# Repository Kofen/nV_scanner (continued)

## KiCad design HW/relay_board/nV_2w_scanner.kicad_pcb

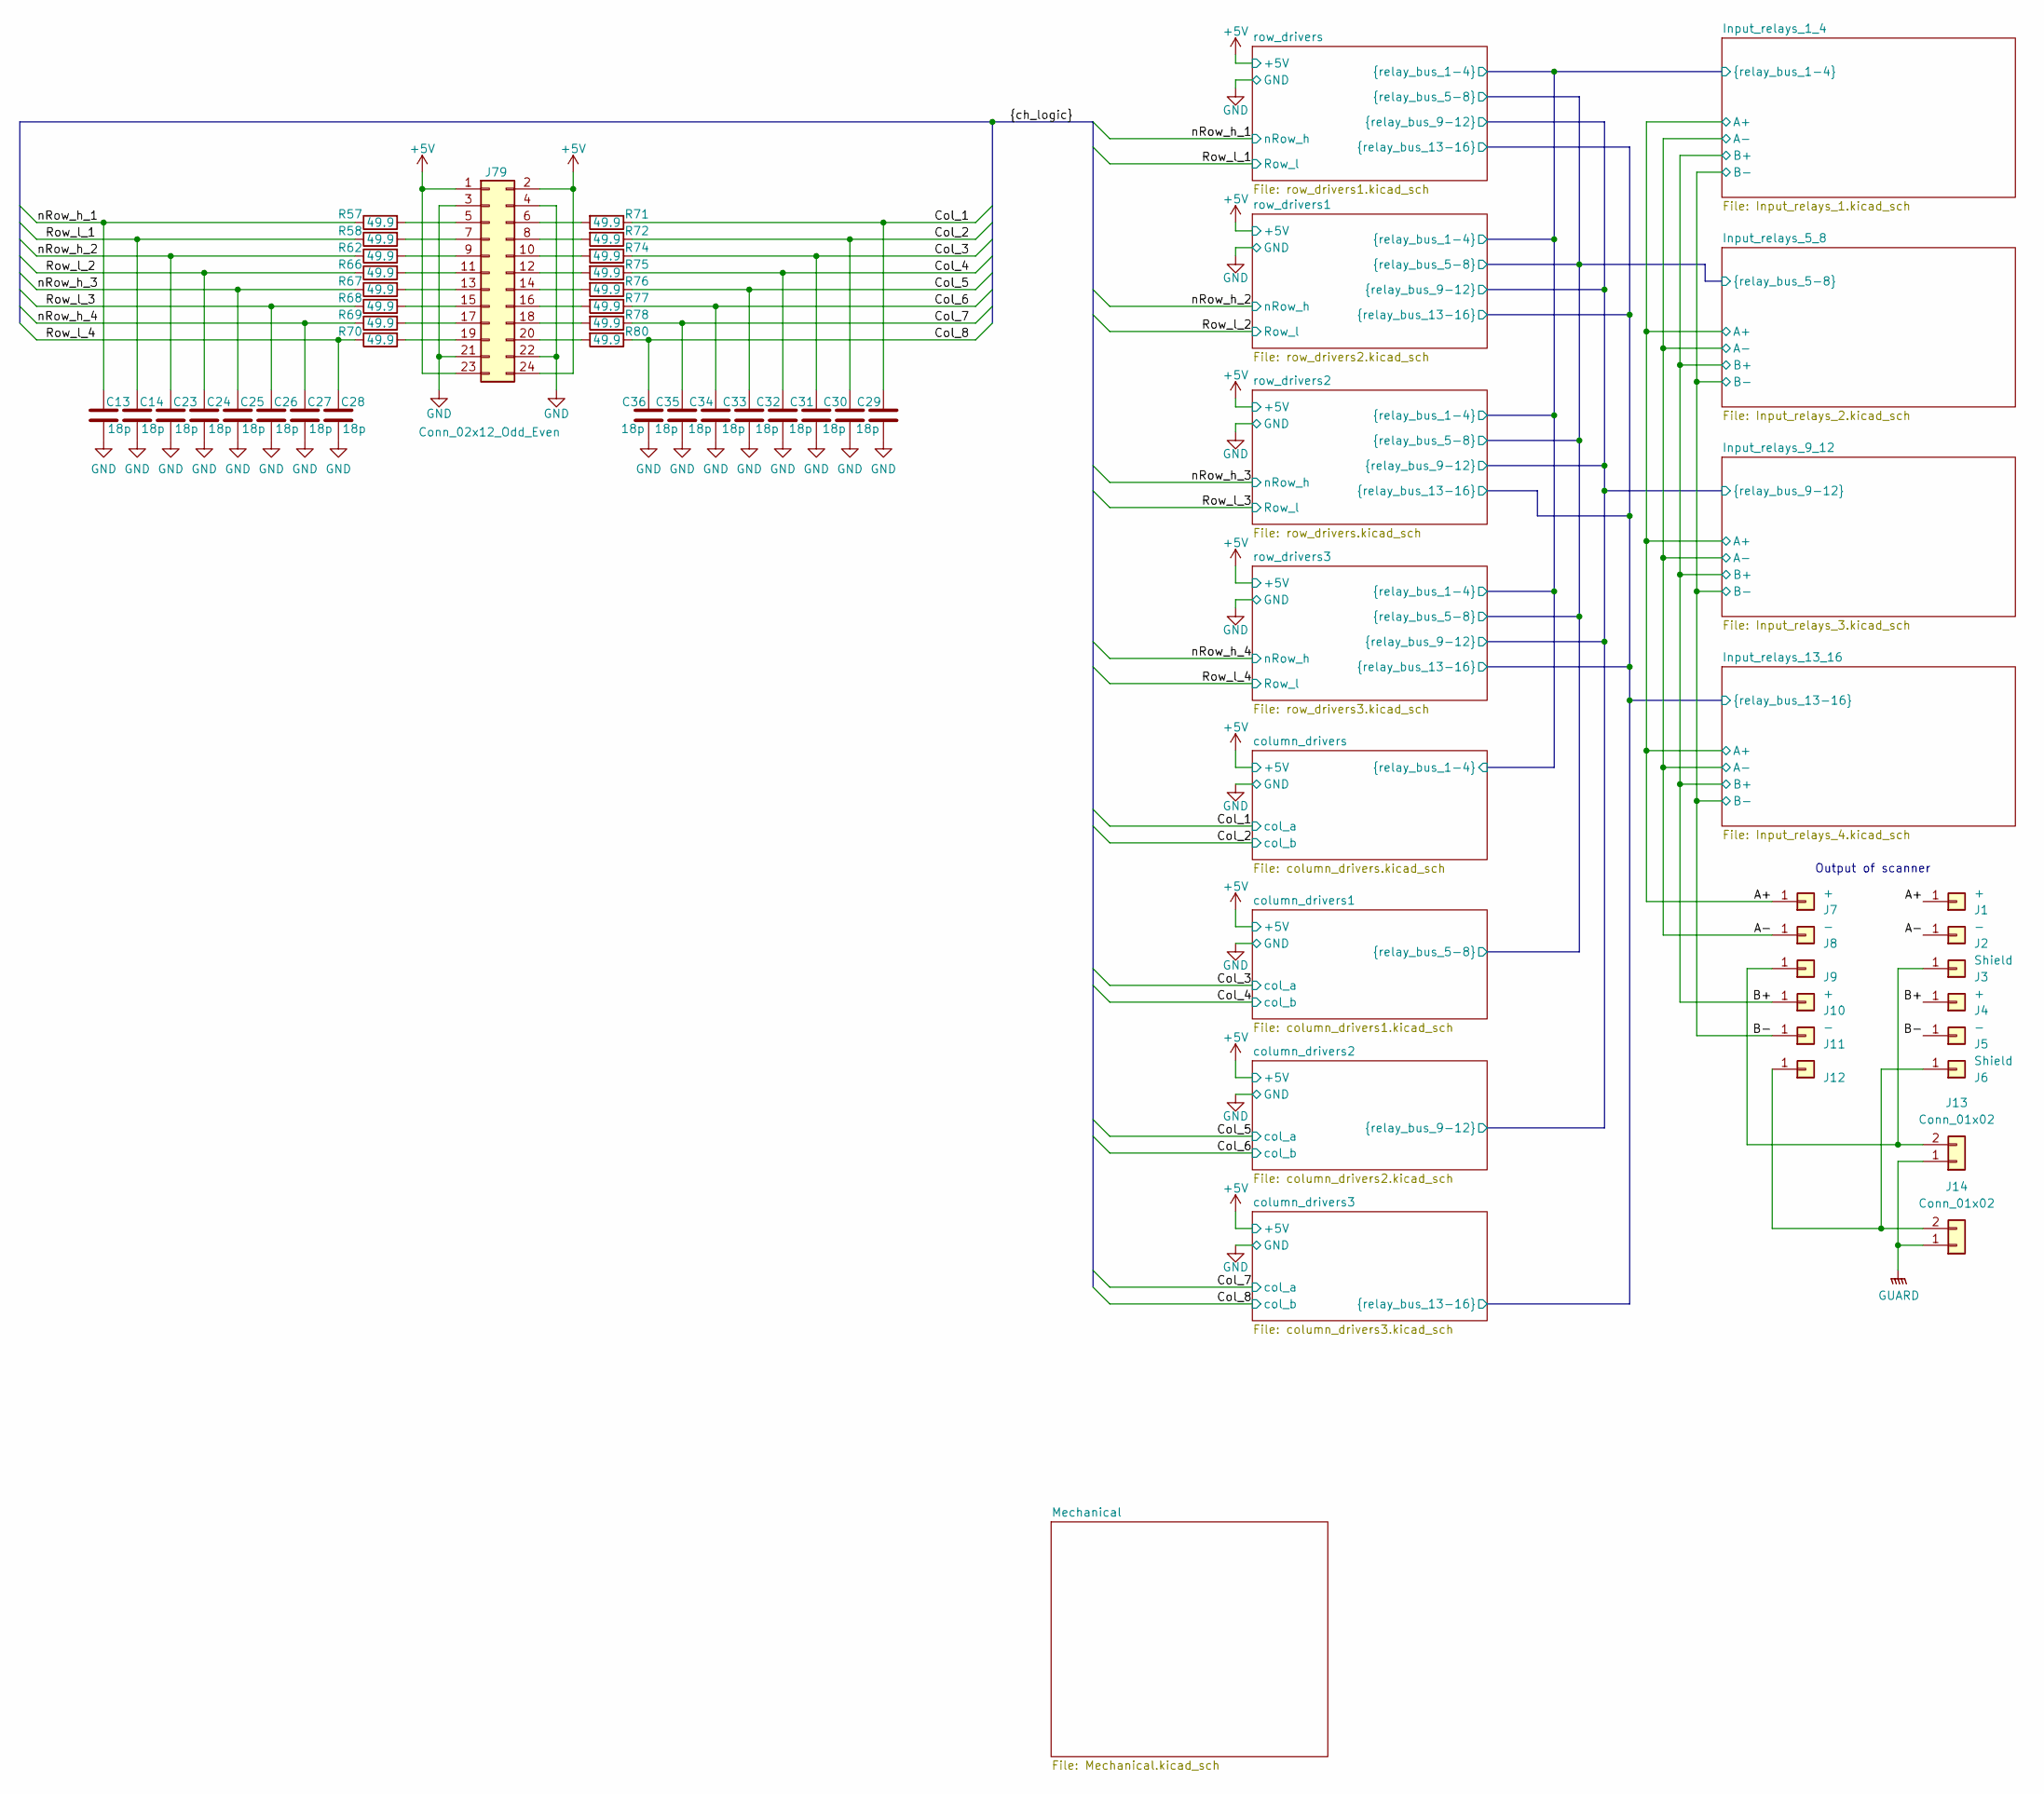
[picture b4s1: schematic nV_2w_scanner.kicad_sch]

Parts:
C13, C14, C23, C24, C25, C26, C27, C28, C29, C30, C31, C32, C33, C34, C35, C36: 18p; C_0402_1005Metric; JLCPCB C1549
J1, J4, J7, J10: +; SolderWirePad_1x01_SMD_3x5mm
J2, J5, J8, J11: -; SolderWirePad_1x01_SMD_3x5mm
J3, J6, J9, J12: Shield; SolderWirePad_1x01_SMD_3x5mm
J13, J14: Conn_01x02; PinHeader_1x02_P2.54mm_Vertical
J79: Conn_02x12_Odd_Even; PinHeader_2x12_P2.54mm_Vertical
R57, R58, R62, R66, R67, R68, R69, R70, R71, R72, R74, R75, R76, R77, R78, R80: 49.9; R_0402_1005Metric

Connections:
+5V: J79.1, J79.2, J79.23, J79.24; also elsewhere on the board
/A+: J1.1, J7.1; also elsewhere on the board
/A-: J2.1, J8.1; also elsewhere on the board
/B+: J4.1, J10.1; also elsewhere on the board
/B-: J5.1, J11.1; also elsewhere on the board
/Col_1: C29.1, R71.1; also elsewhere on the board
/Col_2: C30.1, R72.1; also elsewhere on the board
/Col_3: C31.1, R74.1; also elsewhere on the board
/Col_4: C32.1, R75.1; also elsewhere on the board
/Col_5: C33.1, R76.1; also elsewhere on the board
/Col_6: C34.1, R77.1; also elsewhere on the board
/Col_7: C35.1, R78.1; also elsewhere on the board
/Col_8: C36.1, R80.1; also elsewhere on the board
/Row_l_1: C14.1, R58.1; also elsewhere on the board
/Row_l_2: C24.1, R66.1; also elsewhere on the board
/Row_l_3: C26.1, R68.1; also elsewhere on the board
/Row_l_4: C28.1, R70.1; also elsewhere on the board
/nRow_h_1: C13.1, R57.1; also elsewhere on the board
/nRow_h_2: C23.1, R62.1; also elsewhere on the board
/nRow_h_3: C25.1, R67.1; also elsewhere on the board
/nRow_h_4: C27.1, R69.1; also elsewhere on the board
GND: C13.2, C14.2, C23.2, C24.2, C25.2, C26.2, C27.2, C28.2, C29.2, C30.2, C31.2, C32.2, C33.2, C34.2, C35.2, C36.2, J79.3, J79.4, J79.21, J79.22; also elsewhere on the board
GUARD: J13.1, J14.1; also elsewhere on the board
unnamed: J6.1, J12.1, J14.2
unnamed: J3.1, J9.1, J13.2
unnamed: J79.5, R57.2
unnamed: J79.6, R71.2
unnamed: J79.7, R58.2
unnamed: J79.8, R72.2
unnamed: J79.9, R62.2
unnamed: J79.10, R74.2
unnamed: J79.11, R66.2
unnamed: J79.12, R75.2
unnamed: J79.13, R67.2
unnamed: J79.14, R76.2
unnamed: J79.15, R68.2
unnamed: J79.16, R77.2
unnamed: J79.17, R69.2
unnamed: J79.18, R78.2
unnamed: J79.19, R70.2
unnamed: J79.20, R80.2

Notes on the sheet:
Output of scanner

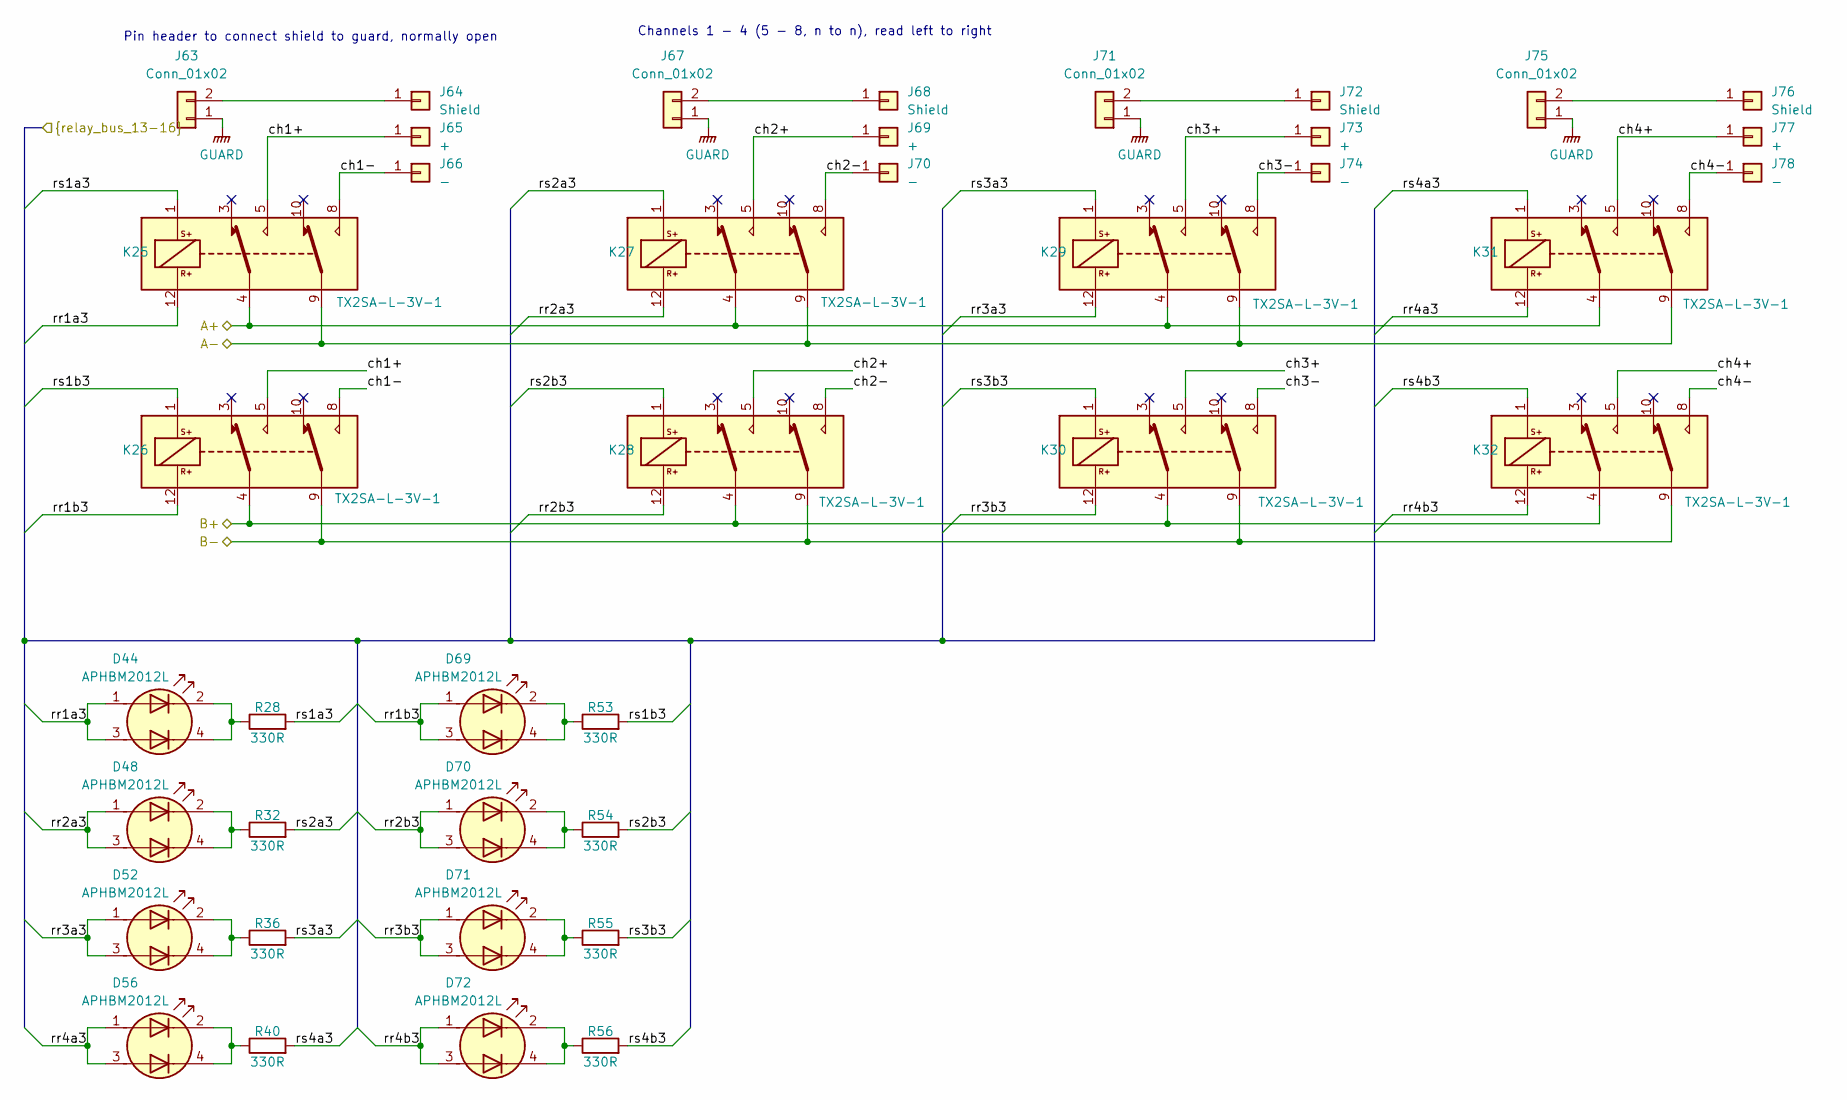
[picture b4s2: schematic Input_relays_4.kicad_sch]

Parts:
D44, D48, D52, D56, D69, D70, D71, D72: APHBM2012L; LED_Kingbright_APHBM2012_2x1.25mm
J63, J67, J71, J75: Conn_01x02; PinHeader_1x02_P2.54mm_Vertical
J64, J68, J72, J76: Shield; SolderWirePad_1x01_SMD_3x5mm
J65, J69, J73, J77: +; SolderWirePad_1x01_SMD_3x5mm
J66, J70, J74, J78: -; SolderWirePad_1x01_SMD_3x5mm
K25, K26, K27, K28, K29, K30, K31, K32: TX2SA-L-3V-1; Relay_DPDT_Omron_G6S-2F
R28, R32, R36, R40, R53, R54, R55, R56: 330R; R_0603_1608Metric

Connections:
/A+: K25.4, K27.4, K29.4, K31.4; also elsewhere on the board
/A-: K25.9, K27.9, K29.9, K31.9; also elsewhere on the board
/B+: K26.4, K28.4, K30.4, K32.4; also elsewhere on the board
/B-: K26.9, K28.9, K30.9, K32.9; also elsewhere on the board
/Input_relays_13_16/ch1+: J65.1, K25.5, K26.5
/Input_relays_13_16/ch1-: J66.1, K25.8, K26.8
/Input_relays_13_16/ch2+: J69.1, K27.5, K28.5
/Input_relays_13_16/ch2-: J70.1, K27.8, K28.8
/Input_relays_13_16/ch3+: J73.1, K29.5, K30.5
/Input_relays_13_16/ch3-: J74.1, K29.8, K30.8
/Input_relays_13_16/ch4+: J77.1, K31.5, K32.5
/Input_relays_13_16/ch4-: J78.1, K31.8, K32.8
/Input_relays_13_16/rr1a3: D44.1 (A1), D44.3 (A2), K25.12; also elsewhere on the board
/Input_relays_13_16/rr1b3: D69.1 (A1), D69.3 (A2), K26.12; also elsewhere on the board
/Input_relays_13_16/rr2a3: D48.1 (A1), D48.3 (A2), K27.12; also elsewhere on the board
/Input_relays_13_16/rr2b3: D70.1 (A1), D70.3 (A2), K28.12; also elsewhere on the board
/Input_relays_13_16/rr3a3: D52.1 (A1), D52.3 (A2), K29.12; also elsewhere on the board
/Input_relays_13_16/rr3b3: D71.1 (A1), D71.3 (A2), K30.12; also elsewhere on the board
/Input_relays_13_16/rr4a3: D56.1 (A1), D56.3 (A2), K31.12; also elsewhere on the board
/Input_relays_13_16/rr4b3: D72.1 (A1), D72.3 (A2), K32.12; also elsewhere on the board
/Input_relays_13_16/rs4a3: K25.1, K27.1, K29.1, K31.1, R28.2, R32.2, R36.2, R40.2; also elsewhere on the board
/Input_relays_13_16/rs4b3: K26.1, K28.1, K30.1, K32.1, R53.2, R54.2, R55.2, R56.2; also elsewhere on the board
GUARD: J63.1, J67.1, J71.1, J75.1; also elsewhere on the board
unnamed: D44.2 (K1), D44.4 (K2), R28.1
unnamed: D48.2 (K1), D48.4 (K2), R32.1
unnamed: D52.2 (K1), D52.4 (K2), R36.1
unnamed: D56.2 (K1), D56.4 (K2), R40.1
unnamed: D69.2 (K1), D69.4 (K2), R53.1
unnamed: D70.2 (K1), D70.4 (K2), R54.1
unnamed: D71.2 (K1), D71.4 (K2), R55.1
unnamed: D72.2 (K1), D72.4 (K2), R56.1
unnamed: J63.2, J64.1
unnamed: J67.2, J68.1
unnamed: J71.2, J72.1
unnamed: J75.2, J76.1

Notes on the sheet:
Pin header to connect shield to guard, normally open
Channels 1 - 4 (5 - 8, n to n), read left to right

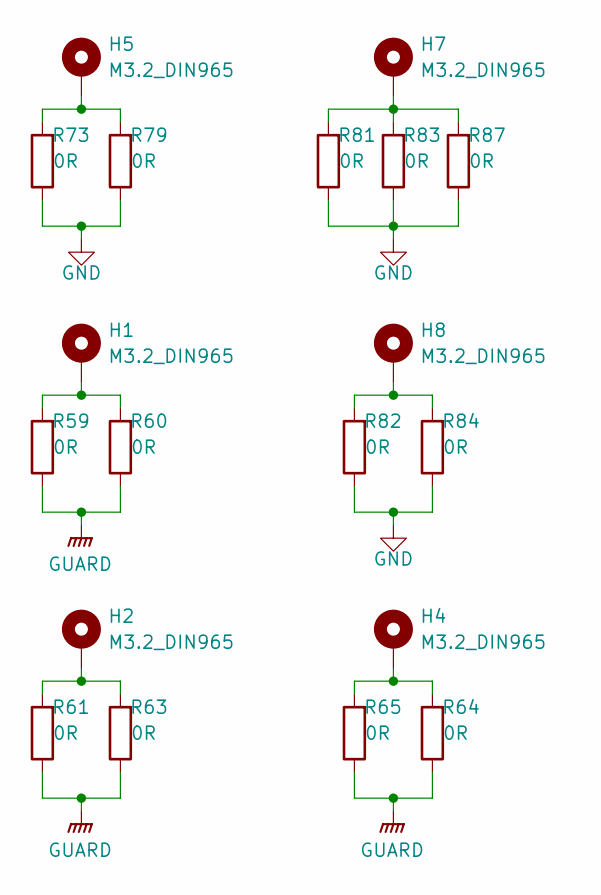
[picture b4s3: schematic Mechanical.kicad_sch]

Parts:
H1, H2, H4, H5, H7, H8: M3.2_DIN965; MountingHole_3.2mm_M3_DIN965_Pad
R59, R60, R61, R63, R64, R65, R73, R79, R81, R82, R83, R84, R87: 0R; R_0805_2012Metric

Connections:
GND: R73.1, R79.1, R81.1, R82.1, R83.1, R84.1, R87.1; also elsewhere on the board
GUARD: R59.1, R60.1, R61.1, R63.1, R64.1, R65.1; also elsewhere on the board
unnamed: H1.1, R59.2, R60.2
unnamed: H2.1, R61.2, R63.2
unnamed: H4.1, R64.2, R65.2
unnamed: H5.1, R73.2, R79.2
unnamed: H7.1, R81.2, R83.2, R87.2
unnamed: H8.1, R82.2, R84.2

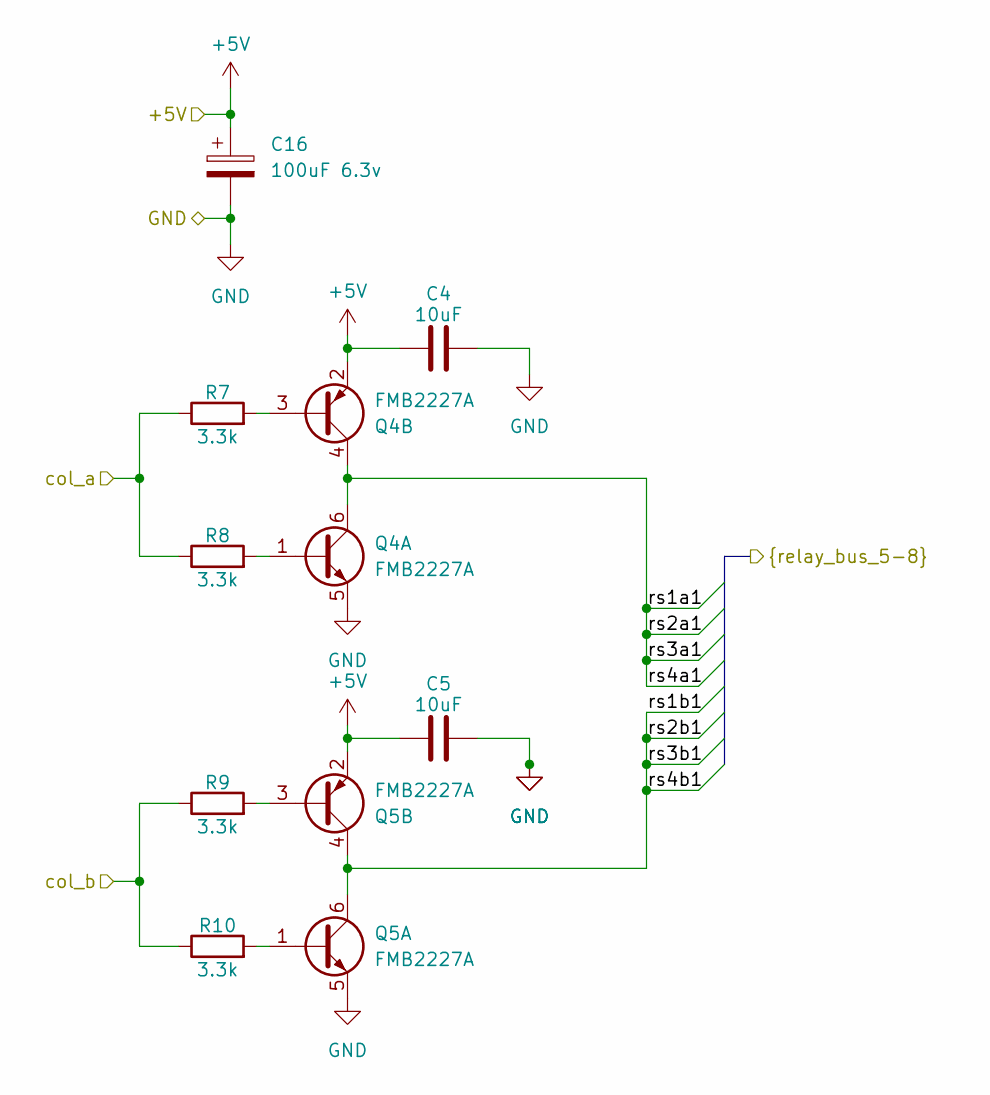
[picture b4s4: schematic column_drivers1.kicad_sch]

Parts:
C4, C5: 10uF; C_0603_1608Metric
C16: 100uF 6.3v; CP_EIA-7343-31_Kemet-D
Q4, Q5: FMB2227A; SuperSOT-6
R7, R8, R9, R10: 3.3k; R_0603_1608Metric

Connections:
+5V: C4.1, C5.1, C16.1, Q4.2 (E2), Q5.2 (E2); also elsewhere on the board
/Col_3: R7.1, R8.1; also elsewhere on the board
/Col_4: R9.1, R10.1; also elsewhere on the board
/Input_relays_5_8/rs2b1: Q5.4 (C2), Q5.6 (C1); also elsewhere on the board
/Input_relays_5_8/rs3a1: Q4.4 (C2), Q4.6 (C1); also elsewhere on the board
GND: C4.2, C5.2, C16.2, Q4.5 (E1), Q5.5 (E1); also elsewhere on the board
unnamed: Q4.1 (B1), R8.2
unnamed: Q4.3 (B2), R7.2
unnamed: Q5.1 (B1), R10.2
unnamed: Q5.3 (B2), R9.2

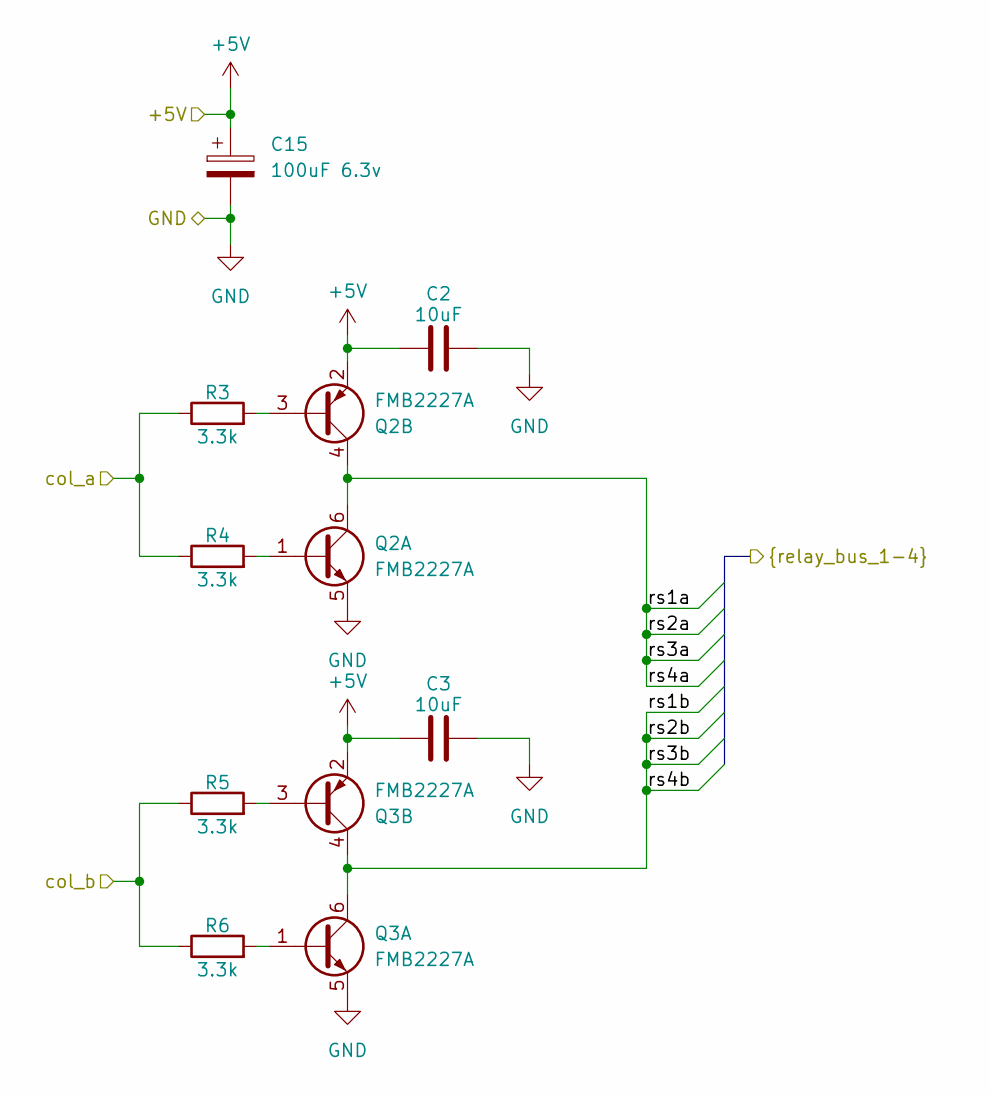
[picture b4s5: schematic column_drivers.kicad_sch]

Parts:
C2, C3: 10uF; C_0603_1608Metric
C15: 100uF 6.3v; CP_EIA-7343-31_Kemet-D
Q2, Q3: FMB2227A; SuperSOT-6
R3, R4, R5, R6: 3.3k; R_0603_1608Metric

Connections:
+5V: C2.1, C3.1, C15.1, Q2.2 (E2), Q3.2 (E2); also elsewhere on the board
/Col_1: R3.1, R4.1; also elsewhere on the board
/Col_2: R5.1, R6.1; also elsewhere on the board
/Input_relays_1_4/rs1a: Q2.4 (C2), Q2.6 (C1); also elsewhere on the board
/Input_relays_1_4/rs3b: Q3.4 (C2), Q3.6 (C1); also elsewhere on the board
GND: C2.2, C3.2, C15.2, Q2.5 (E1), Q3.5 (E1); also elsewhere on the board
unnamed: Q2.1 (B1), R4.2
unnamed: Q2.3 (B2), R3.2
unnamed: Q3.1 (B1), R6.2
unnamed: Q3.3 (B2), R5.2

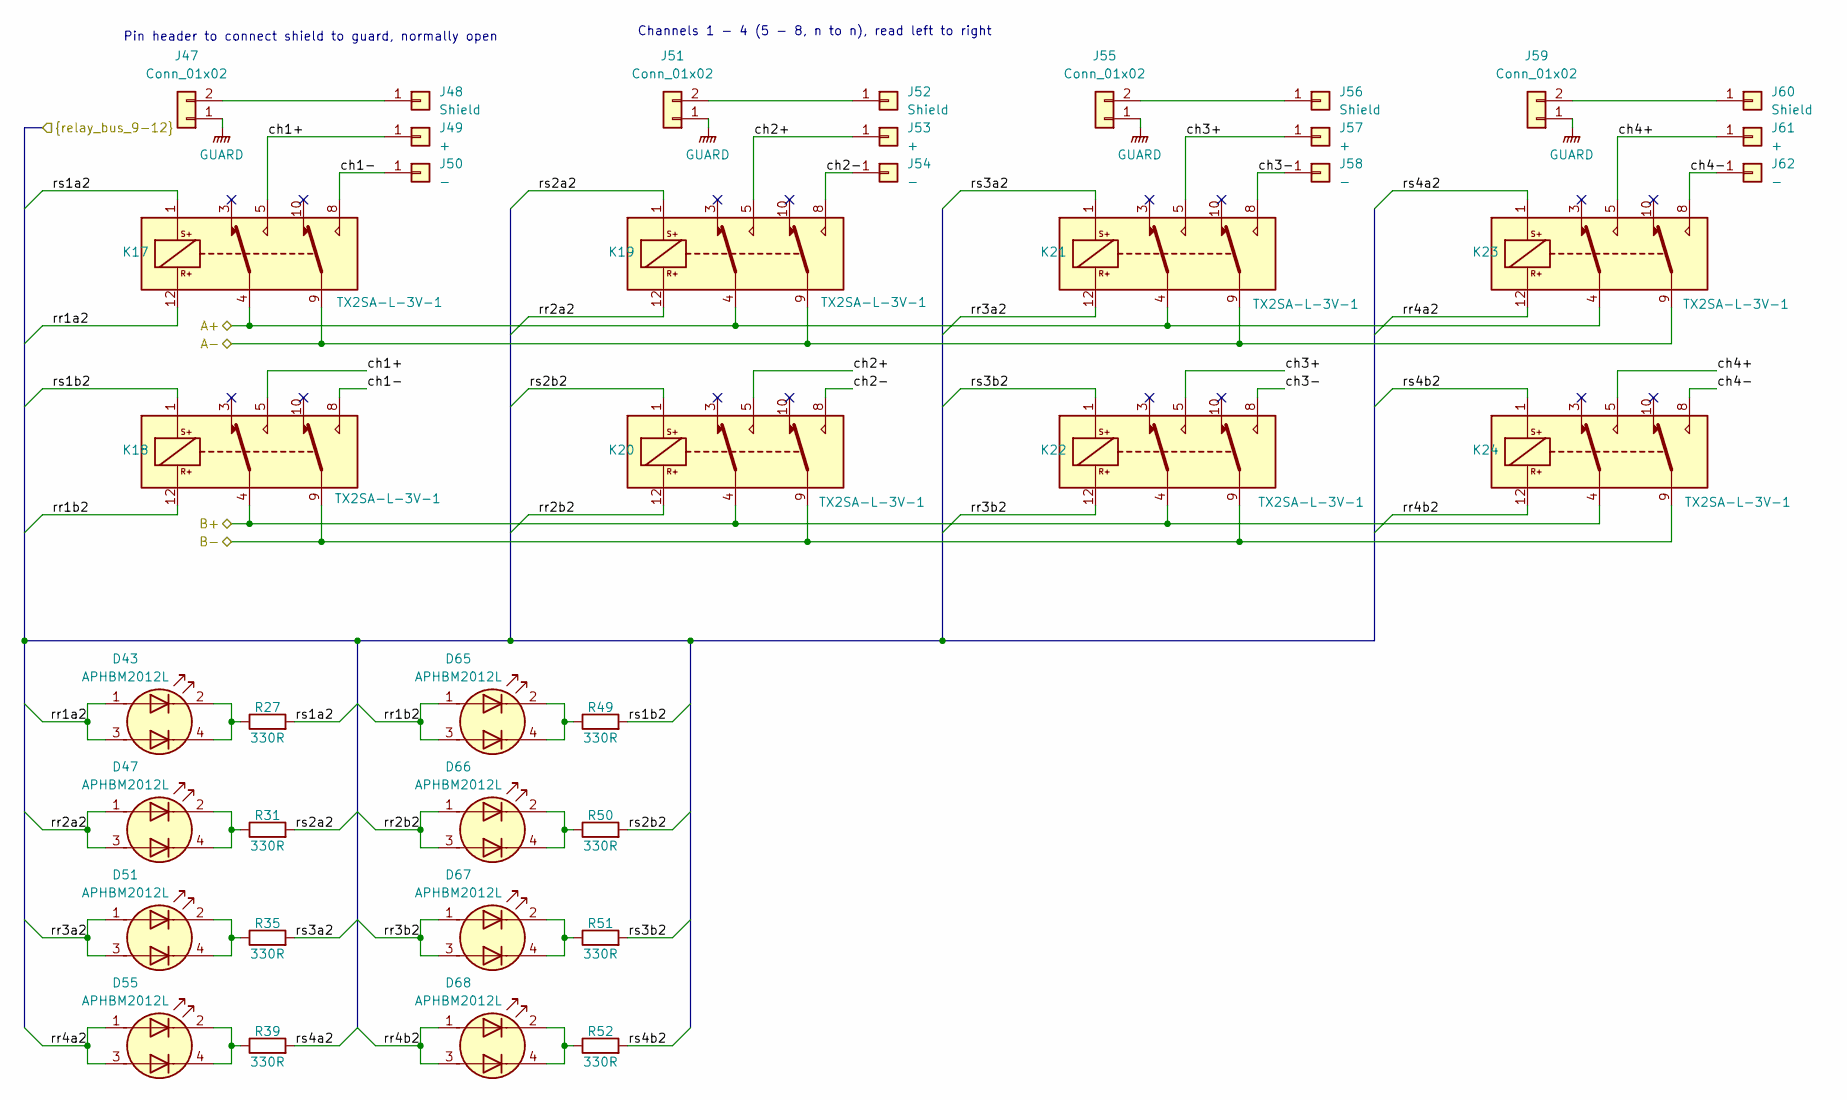
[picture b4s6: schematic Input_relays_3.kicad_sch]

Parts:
D43, D47, D51, D55, D65, D66, D67, D68: APHBM2012L; LED_Kingbright_APHBM2012_2x1.25mm
J47, J51, J55, J59: Conn_01x02; PinHeader_1x02_P2.54mm_Vertical
J48, J52, J56, J60: Shield; SolderWirePad_1x01_SMD_3x5mm
J49, J53, J57, J61: +; SolderWirePad_1x01_SMD_3x5mm
J50, J54, J58, J62: -; SolderWirePad_1x01_SMD_3x5mm
K17, K18, K19, K20, K21, K22, K23, K24: TX2SA-L-3V-1; Relay_DPDT_Omron_G6S-2F
R27, R31, R35, R39, R49, R50, R51, R52: 330R; R_0603_1608Metric

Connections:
/A+: K17.4, K19.4, K21.4, K23.4; also elsewhere on the board
/A-: K17.9, K19.9, K21.9, K23.9; also elsewhere on the board
/B+: K18.4, K20.4, K22.4, K24.4; also elsewhere on the board
/B-: K18.9, K20.9, K22.9, K24.9; also elsewhere on the board
/Input_relays_9_12/ch1+: J49.1, K17.5, K18.5
/Input_relays_9_12/ch1-: J50.1, K17.8, K18.8
/Input_relays_9_12/ch2+: J53.1, K19.5, K20.5
/Input_relays_9_12/ch2-: J54.1, K19.8, K20.8
/Input_relays_9_12/ch3+: J57.1, K21.5, K22.5
/Input_relays_9_12/ch3-: J58.1, K21.8, K22.8
/Input_relays_9_12/ch4+: J61.1, K23.5, K24.5
/Input_relays_9_12/ch4-: J62.1, K23.8, K24.8
/Input_relays_9_12/rr1a2: D43.1 (A1), D43.3 (A2), K17.12; also elsewhere on the board
/Input_relays_9_12/rr1b2: D65.1 (A1), D65.3 (A2), K18.12; also elsewhere on the board
/Input_relays_9_12/rr2a2: D47.1 (A1), D47.3 (A2), K19.12; also elsewhere on the board
/Input_relays_9_12/rr2b2: D66.1 (A1), D66.3 (A2), K20.12; also elsewhere on the board
/Input_relays_9_12/rr3a2: D51.1 (A1), D51.3 (A2), K21.12; also elsewhere on the board
/Input_relays_9_12/rr3b2: D67.1 (A1), D67.3 (A2), K22.12; also elsewhere on the board
/Input_relays_9_12/rr4a2: D55.1 (A1), D55.3 (A2), K23.12; also elsewhere on the board
/Input_relays_9_12/rr4b2: D68.1 (A1), D68.3 (A2), K24.12; also elsewhere on the board
/Input_relays_9_12/rs3a2: K17.1, K19.1, K21.1, K23.1, R27.2, R31.2, R35.2, R39.2; also elsewhere on the board
/Input_relays_9_12/rs3b2: K18.1, K20.1, K22.1, K24.1, R49.2, R50.2, R51.2, R52.2; also elsewhere on the board
GUARD: J47.1, J51.1, J55.1, J59.1; also elsewhere on the board
unnamed: D43.2 (K1), D43.4 (K2), R27.1
unnamed: D47.2 (K1), D47.4 (K2), R31.1
unnamed: D51.2 (K1), D51.4 (K2), R35.1
unnamed: D55.2 (K1), D55.4 (K2), R39.1
unnamed: D65.2 (K1), D65.4 (K2), R49.1
unnamed: D66.2 (K1), D66.4 (K2), R50.1
unnamed: D67.2 (K1), D67.4 (K2), R51.1
unnamed: D68.2 (K1), D68.4 (K2), R52.1
unnamed: J47.2, J48.1
unnamed: J51.2, J52.1
unnamed: J55.2, J56.1
unnamed: J59.2, J60.1

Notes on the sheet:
Pin header to connect shield to guard, normally open
Channels 1 - 4 (5 - 8, n to n), read left to right

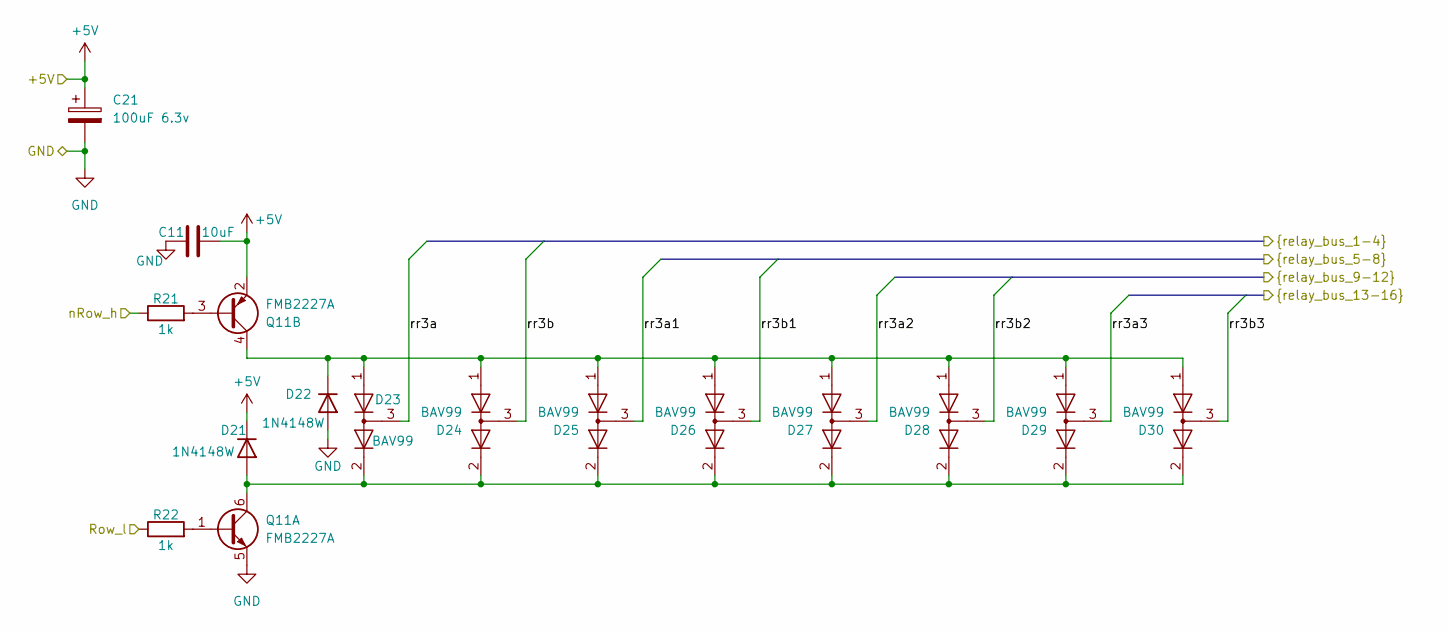
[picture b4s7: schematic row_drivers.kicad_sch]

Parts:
C11: 10uF; C_0603_1608Metric
C21: 100uF 6.3v; CP_EIA-7343-31_Kemet-D
D21, D22: 1N4148W; D_SOD-123
D23, D24, D25, D26, D27, D28, D29, D30: BAV99; SOT-23
Q11: FMB2227A; SuperSOT-6
R21, R22: 1k; R_0603_1608Metric

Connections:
+5V: C11.2, C21.1, D21.1 (K), Q11.2 (E2); also elsewhere on the board
/Input_relays_1_4/rr3a: D23.3 (K); also elsewhere on the board
/Input_relays_1_4/rr3b: D24.3 (K); also elsewhere on the board
/Input_relays_5_8/rr3a1: D25.3 (K); also elsewhere on the board
/Input_relays_5_8/rr3b1: D26.3 (K); also elsewhere on the board
/Input_relays_9_12/rr3a2: D27.3 (K); also elsewhere on the board
/Input_relays_9_12/rr3b2: D28.3 (K); also elsewhere on the board
/Input_relays_13_16/rr3a3: D29.3 (K); also elsewhere on the board
/Input_relays_13_16/rr3b3: D30.3 (K); also elsewhere on the board
/Row_l_3: R22.1; also elsewhere on the board
/nRow_h_3: R21.1; also elsewhere on the board
GND: C11.1, C21.2, D22.2 (A), Q11.5 (E1); also elsewhere on the board
unnamed: D21.2 (A), D23.2 (A), D24.2 (A), D25.2 (A), D26.2 (A), D27.2 (A), D28.2 (A), D29.2 (A), D30.2 (A), Q11.6 (C1)
unnamed: D22.1 (K), D23.1 (K), D24.1 (K), D25.1 (K), D26.1 (K), D27.1 (K), D28.1 (K), D29.1 (K), D30.1 (K), Q11.4 (C2)
unnamed: Q11.1 (B1), R22.2
unnamed: Q11.3 (B2), R21.2

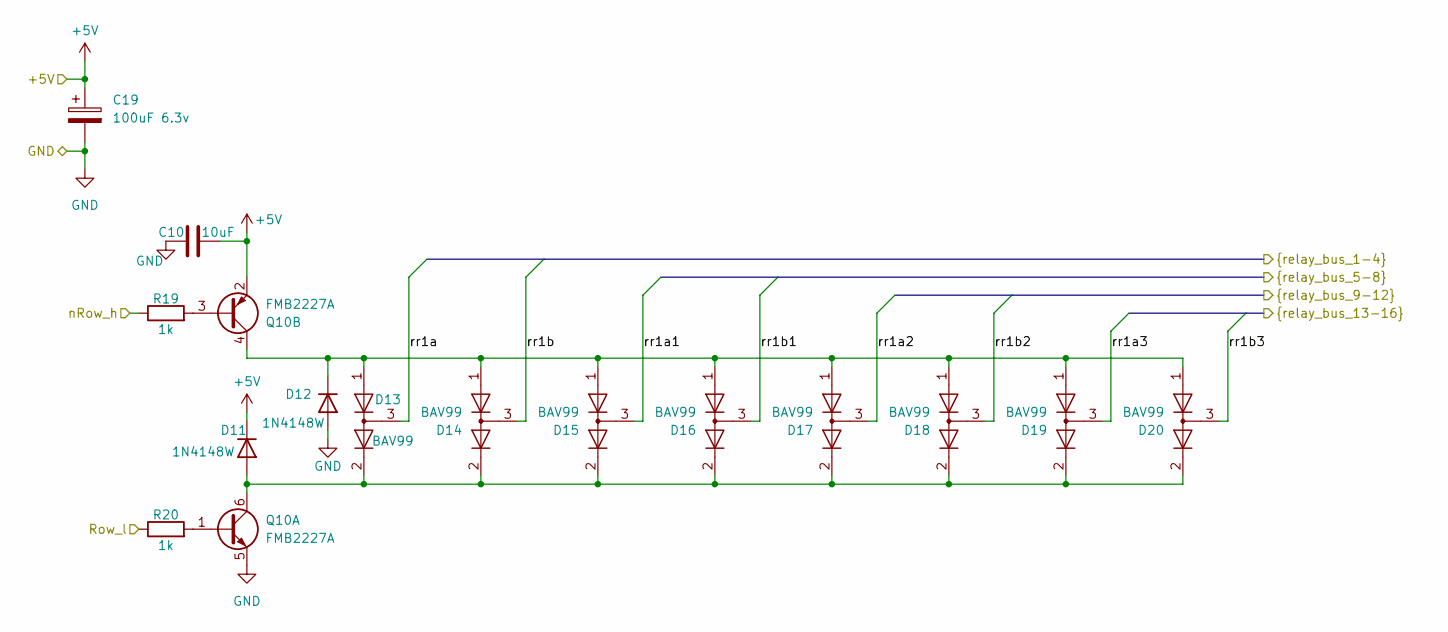
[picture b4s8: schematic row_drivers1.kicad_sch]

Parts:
C10: 10uF; C_0603_1608Metric
C19: 100uF 6.3v; CP_EIA-7343-31_Kemet-D
D11, D12: 1N4148W; D_SOD-123
D13, D14, D15, D16, D17, D18, D19, D20: BAV99; SOT-23
Q10: FMB2227A; SuperSOT-6
R19, R20: 1k; R_0603_1608Metric

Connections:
+5V: C10.2, C19.1, D11.1 (K), Q10.2 (E2); also elsewhere on the board
/Input_relays_1_4/rr1a: D13.3 (K); also elsewhere on the board
/Input_relays_1_4/rr1b: D14.3 (K); also elsewhere on the board
/Input_relays_5_8/rr1a1: D15.3 (K); also elsewhere on the board
/Input_relays_5_8/rr1b1: D16.3 (K); also elsewhere on the board
/Input_relays_9_12/rr1a2: D17.3 (K); also elsewhere on the board
/Input_relays_9_12/rr1b2: D18.3 (K); also elsewhere on the board
/Input_relays_13_16/rr1a3: D19.3 (K); also elsewhere on the board
/Input_relays_13_16/rr1b3: D20.3 (K); also elsewhere on the board
/Row_l_1: R20.1; also elsewhere on the board
/nRow_h_1: R19.1; also elsewhere on the board
GND: C10.1, C19.2, D12.2 (A), Q10.5 (E1); also elsewhere on the board
unnamed: D11.2 (A), D13.2 (A), D14.2 (A), D15.2 (A), D16.2 (A), D17.2 (A), D18.2 (A), D19.2 (A), D20.2 (A), Q10.6 (C1)
unnamed: D12.1 (K), D13.1 (K), D14.1 (K), D15.1 (K), D16.1 (K), D17.1 (K), D18.1 (K), D19.1 (K), D20.1 (K), Q10.4 (C2)
unnamed: Q10.1 (B1), R20.2
unnamed: Q10.3 (B2), R19.2

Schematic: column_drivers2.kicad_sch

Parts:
C6, C7: 10uF; C_0603_1608Metric
C17: 100uF 6.3v; CP_EIA-7343-31_Kemet-D
Q6, Q7: FMB2227A; SuperSOT-6
R11, R12, R13, R14: 3.3k; R_0603_1608Metric

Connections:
+5V: C6.1, C7.1, C17.1, Q6.2 (E2), Q7.2 (E2); also elsewhere on the board
/Col_5: R11.1, R12.1; also elsewhere on the board
/Col_6: R13.1, R14.1; also elsewhere on the board
/Input_relays_9_12/rs3a2: Q6.4 (C2), Q6.6 (C1); also elsewhere on the board
/Input_relays_9_12/rs3b2: Q7.4 (C2), Q7.6 (C1); also elsewhere on the board
GND: C6.2, C7.2, C17.2, Q6.5 (E1), Q7.5 (E1); also elsewhere on the board
unnamed: Q6.1 (B1), R12.2
unnamed: Q6.3 (B2), R11.2
unnamed: Q7.1 (B1), R14.2
unnamed: Q7.3 (B2), R13.2

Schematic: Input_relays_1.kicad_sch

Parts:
D41, D45, D49, D53, D57, D58, D59, D60: APHBM2012L; LED_Kingbright_APHBM2012_2x1.25mm
J15, J19, J23, J27: Conn_01x02; PinHeader_1x02_P2.54mm_Vertical
J16, J20, J24, J28: Shield; SolderWirePad_1x01_SMD_3x5mm
J17, J21, J25, J29: +; SolderWirePad_1x01_SMD_3x5mm
J18, J22, J26, J30: -; SolderWirePad_1x01_SMD_3x5mm
K1, K2, K3, K4, K5, K6, K7, K8: TX2SA-L-3V-1; Relay_DPDT_Omron_G6S-2F
R25, R29, R33, R37, R41, R42, R43, R44: 330R; R_0603_1608Metric

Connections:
/A+: K1.4, K3.4, K5.4, K7.4; also elsewhere on the board
/A-: K1.9, K3.9, K5.9, K7.9; also elsewhere on the board
/B+: K2.4, K4.4, K6.4, K8.4; also elsewhere on the board
/B-: K2.9, K4.9, K6.9, K8.9; also elsewhere on the board
/Input_relays_1_4/ch1+: J17.1, K1.5, K2.5
/Input_relays_1_4/ch1-: J18.1, K1.8, K2.8
/Input_relays_1_4/ch2+: J21.1, K3.5, K4.5
/Input_relays_1_4/ch2-: J22.1, K3.8, K4.8
/Input_relays_1_4/ch3+: J25.1, K5.5, K6.5
/Input_relays_1_4/ch3-: J26.1, K5.8, K6.8
/Input_relays_1_4/ch4+: J29.1, K7.5, K8.5
/Input_relays_1_4/ch4-: J30.1, K7.8, K8.8
/Input_relays_1_4/rr1a: D41.1 (A1), D41.3 (A2), K1.12; also elsewhere on the board
/Input_relays_1_4/rr1b: D57.1 (A1), D57.3 (A2), K2.12; also elsewhere on the board
/Input_relays_1_4/rr2a: D45.1 (A1), D45.3 (A2), K3.12; also elsewhere on the board
/Input_relays_1_4/rr2b: D58.1 (A1), D58.3 (A2), K4.12; also elsewhere on the board
/Input_relays_1_4/rr3a: D49.1 (A1), D49.3 (A2), K5.12; also elsewhere on the board
/Input_relays_1_4/rr3b: D59.1 (A1), D59.3 (A2), K6.12; also elsewhere on the board
/Input_relays_1_4/rr4a: D53.1 (A1), D53.3 (A2), K7.12; also elsewhere on the board
/Input_relays_1_4/rr4b: D60.1 (A1), D60.3 (A2), K8.12; also elsewhere on the board
/Input_relays_1_4/rs1a: K1.1, K3.1, K5.1, K7.1, R25.2, R29.2, R33.2, R37.2; also elsewhere on the board
/Input_relays_1_4/rs3b: K2.1, K4.1, K6.1, K8.1, R41.2, R42.2, R43.2, R44.2; also elsewhere on the board
GUARD: J15.1, J19.1, J23.1, J27.1; also elsewhere on the board
unnamed: D41.2 (K1), D41.4 (K2), R25.1
unnamed: D45.2 (K1), D45.4 (K2), R29.1
unnamed: D49.2 (K1), D49.4 (K2), R33.1
unnamed: D53.2 (K1), D53.4 (K2), R37.1
unnamed: D57.2 (K1), D57.4 (K2), R41.1
unnamed: D58.2 (K1), D58.4 (K2), R42.1
unnamed: D59.2 (K1), D59.4 (K2), R43.1
unnamed: D60.2 (K1), D60.4 (K2), R44.1
unnamed: J15.2, J16.1
unnamed: J19.2, J20.1
unnamed: J23.2, J24.1
unnamed: J27.2, J28.1

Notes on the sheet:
Pin header to connect shield to guard, normally open
Channels 1 - 4 (5 - 8, n to n), read left to right

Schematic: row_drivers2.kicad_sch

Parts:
C1: 10uF; C_0603_1608Metric
C20: 100uF 6.3v; CP_EIA-7343-31_Kemet-D
D1, D2: 1N4148W; D_SOD-123
D3, D4, D5, D6, D7, D8, D9, D10: BAV99; SOT-23
Q1: FMB2227A; SuperSOT-6
R1, R2: 1k; R_0603_1608Metric

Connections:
+5V: C1.2, C20.1, D1.1 (K), Q1.2 (E2); also elsewhere on the board
/Input_relays_1_4/rr2a: D3.3 (K); also elsewhere on the board
/Input_relays_1_4/rr2b: D4.3 (K); also elsewhere on the board
/Input_relays_5_8/rr2a1: D5.3 (K); also elsewhere on the board
/Input_relays_5_8/rr2b1: D6.3 (K); also elsewhere on the board
/Input_relays_9_12/rr2a2: D7.3 (K); also elsewhere on the board
/Input_relays_9_12/rr2b2: D8.3 (K); also elsewhere on the board
/Input_relays_13_16/rr2a3: D9.3 (K); also elsewhere on the board
/Input_relays_13_16/rr2b3: D10.3 (K); also elsewhere on the board
/Row_l_2: R2.1; also elsewhere on the board
/nRow_h_2: R1.1; also elsewhere on the board
GND: C1.1, C20.2, D2.2 (A), Q1.5 (E1); also elsewhere on the board
unnamed: D1.2 (A), D3.2 (A), D4.2 (A), D5.2 (A), D6.2 (A), D7.2 (A), D8.2 (A), D9.2 (A), D10.2 (A), Q1.6 (C1)
unnamed: D2.1 (K), D3.1 (K), D4.1 (K), D5.1 (K), D6.1 (K), D7.1 (K), D8.1 (K), D9.1 (K), D10.1 (K), Q1.4 (C2)
unnamed: Q1.1 (B1), R2.2
unnamed: Q1.3 (B2), R1.2
